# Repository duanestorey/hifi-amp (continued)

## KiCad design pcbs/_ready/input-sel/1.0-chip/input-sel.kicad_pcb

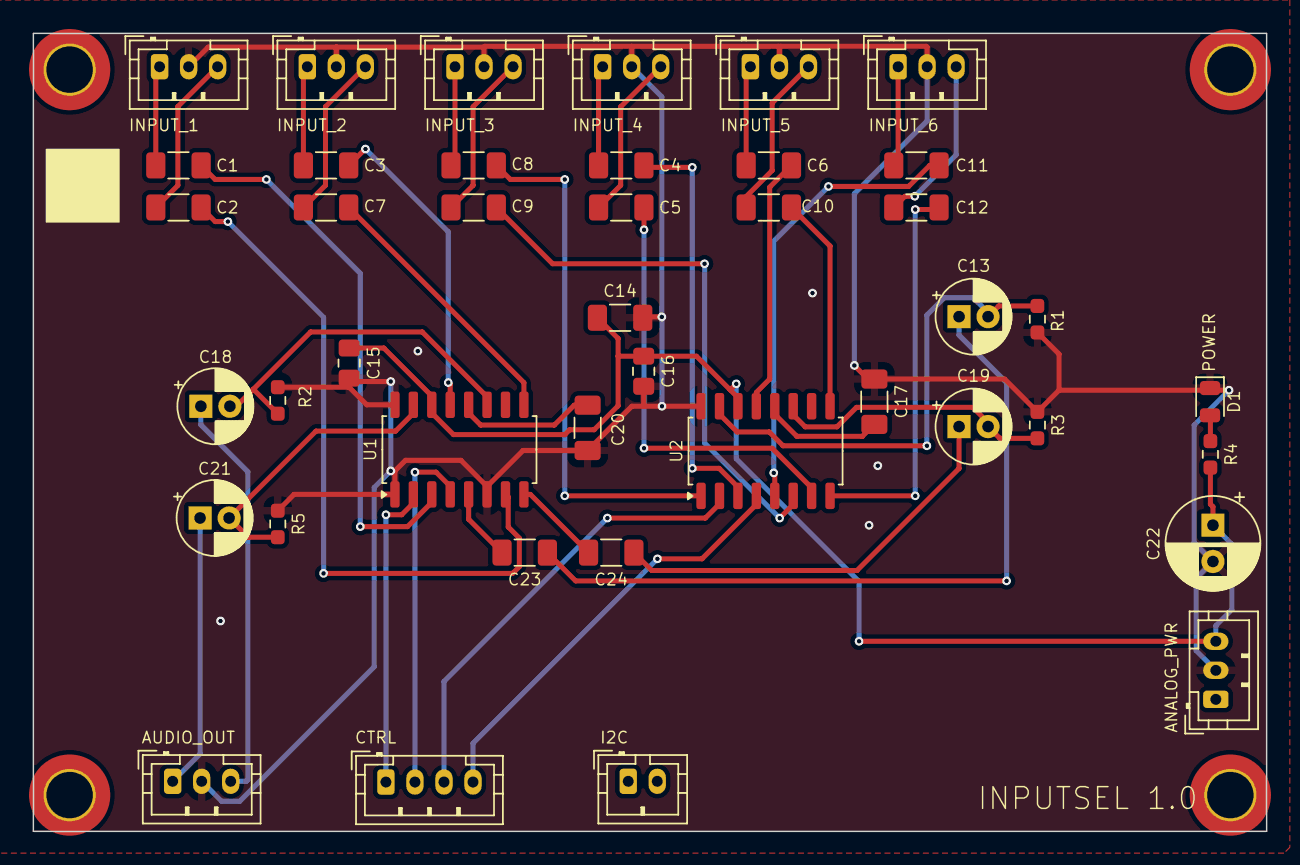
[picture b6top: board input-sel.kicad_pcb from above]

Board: 2 copper layers, 85.0 x 55.0 mm, 46 parts (0 on the bottom side), 43 nets.

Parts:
C1, C2, C3, C4, C5, C6, C7, C8, C9, C10, C11, C12, C23, C24: 0.1u 50V C0G; C_1206_3216Metric_Pad1.33x1.80mm_HandSolder
C13, C18, C19, C21: 4.7u 35V Nichicon Muse; CP_Radial_D5.0mm_P2.00mm
C14, C17, C20: 10U; C_1206_3216Metric_Pad1.33x1.80mm_HandSolder
C15, C16: 0.1u; C_0805_2012Metric_Pad1.18x1.45mm_HandSolder
C22: 470u; CP_Radial_D6.3mm_P2.50mm
D1: RED; LED_0805_2012Metric
H1, H2, H3, H4: MountingHole; MountingHole_3.2mm_M3_DIN965_Pad_TopOnly
J1, J2, J3, J4, J5, J6, J8: Conn_01x03_Pin; JST_PH_B3B-PH-K_1x03_P2.00mm_Vertical
J7: Conn_01x03_Male; JST_PH_B3B-PH-K_1x03_P2.00mm_Vertical
J9: Conn_01x04_Pin; JST_PH_B4B-PH-K_1x04_P2.00mm_Vertical
J10: Conn_01x02_Male; JST_PH_B2B-PH-K_1x02_P2.00mm_Vertical
R1, R2, R3, R5: 100K; R_0603_1608Metric_Pad0.98x0.95mm_HandSolder
R4: 75R; R_0603_1608Metric_Pad0.98x0.95mm_HandSolder
U1, U2: NJM2750; SOP-16_4.4x10.4mm_P1.27mm

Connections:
AGND: C14.2, C15.2, C16.2, C17.1, C20.1, C22.2, D1.1 (K), J1.2, J2.2, J3.2, J4.2, J5.2, J6.2, J7.2, J8.2, R1.1, R2.1, R3.1, R5.1, U1.1 (IN1L), U1.6 (IN1R), U1.16 (GND), U2.16 (GND)
CTRL1: J9.1, U1.2 (CNT1)
CTRL2: J9.2, U1.4 (CNT2)
CTRL3: J9.3, U2.2 (CNT1)
CTRL4: J9.4, U2.4 (CNT2)
EXPAND_L: C13.1, C23.1
EXPAND_R: C19.1, C24.1
unnamed: C11.2, U2.5 (IN4L)
unnamed: C12.2, U2.8 (IN4L)
unnamed: C23.2, U1.5 (IN4L)
unnamed: C24.2, U1.8 (IN4L)
unnamed: D1.2 (A), R4.1
unnamed: C1.2, U1.3 (IN2L)
unnamed: C2.2, U1.7 (IN2R)
unnamed: C3.2, U1.13 (IN3L)
unnamed: C7.2, U1.9 (IN3R)
unnamed: C21.2, R5.2, U1.15 (OUTL)
unnamed: C18.2, R2.2, U1.11 (OUTR)
unnamed: C20.2, U1.12 (VREF)
unnamed: C8.2, U2.1 (IN1L)
unnamed: C9.2, U2.6 (IN1R)
unnamed: C4.2, U2.3 (IN2L)
unnamed: C5.2, U2.7 (IN2R)
unnamed: C6.2, U2.13 (IN3L)
unnamed: C10.2, U2.9 (IN3R)
unnamed: C13.2, R1.2, U2.15 (OUTL)
unnamed: C19.2, R3.2, U2.11 (OUTR)
unnamed: C17.2, U2.12 (VREF)
OUT_L: C21.1, J8.1
OUT_R: C18.1, J8.3
RCA1_L: C1.1, J1.1
RCA1_R: C2.1, J1.3
RCA2_L: C3.1, J2.1
RCA2_R: C7.1, J2.3
RCA3_L: C8.1, J3.1
RCA3_R: C9.1, J3.3
RCA4_L: C4.1, J4.1
RCA4_R: C5.1, J4.3
RCA5_L: C6.1, J5.1
RCA5_R: C10.1, J5.3
RCA6_L: C11.1, J6.1
RCA6_R: C12.1, J6.3
V+: C14.1, C15.1, C16.1, C22.1, J7.3, R4.2, U1.14 (V+), U2.14 (V+)

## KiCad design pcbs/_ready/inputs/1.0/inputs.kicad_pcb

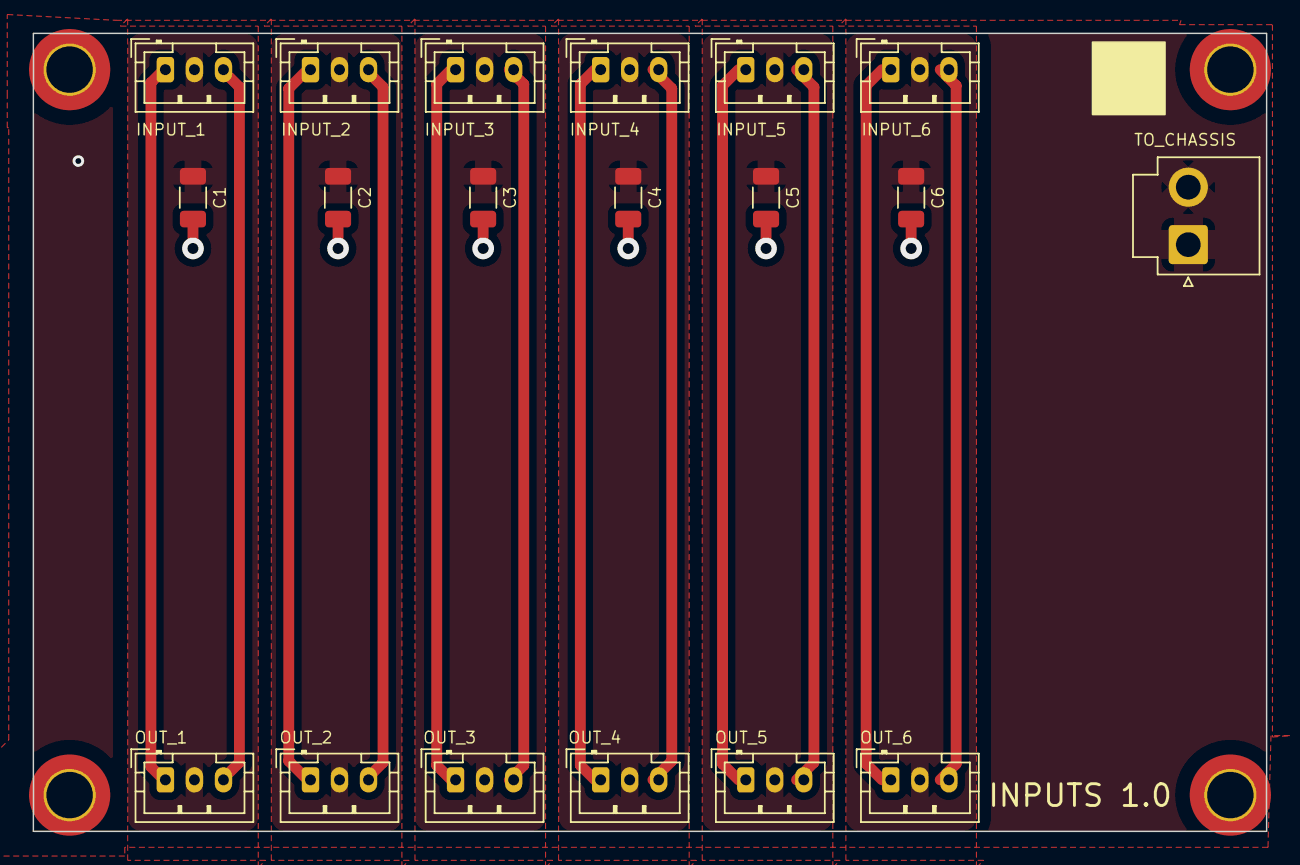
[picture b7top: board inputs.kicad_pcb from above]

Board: 2 copper layers, 85.0 x 55.0 mm, 23 parts (0 on the bottom side), 19 nets.

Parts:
C1, C2, C3, C4, C5, C6: 0.1u 100V; C_1206_3216Metric
H1, H2, H3, H4: MountingHole; MountingHole_3.2mm_M3_DIN965_Pad_TopOnly
J1, J2, J3, J4, J5, J6, J7, J8, J9, J10, J11, J12: Conn_01x03_Pin; JST_PH_B3B-PH-K_1x03_P2.00mm_Vertical
J13: Conn_01x02_Pin; JST_VH_B2P-VH-B_1x02_P3.96mm_Vertical

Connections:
GND_1: C1.1, J1.2, J7.2
GND_2: C2.1, J3.2, J8.2
GND_3: C3.1, J5.2, J9.2
GND_4: C4.1, J2.2, J10.2
GND_5: C5.1, J4.2, J11.2
GND_6: C6.1, J6.2, J12.2
LEFT_1: J1.1, J7.1
LEFT_2: J3.1, J8.1
LEFT_3: J5.1, J9.1
LEFT_4: J2.1, J10.1
LEFT_5: J4.1, J11.1
LEFT_6: J6.1, J12.1
PGND: C1.2, C2.2, C3.2, C4.2, C5.2, C6.2, J13.1, J13.2
RIGHT_1: J1.3, J7.3
RIGHT_2: J3.3, J8.3
RIGHT_3: J5.3, J9.3
RIGHT_4: J2.3, J10.3
RIGHT_5: J4.3, J11.3
RIGHT_6: J6.3, J12.3

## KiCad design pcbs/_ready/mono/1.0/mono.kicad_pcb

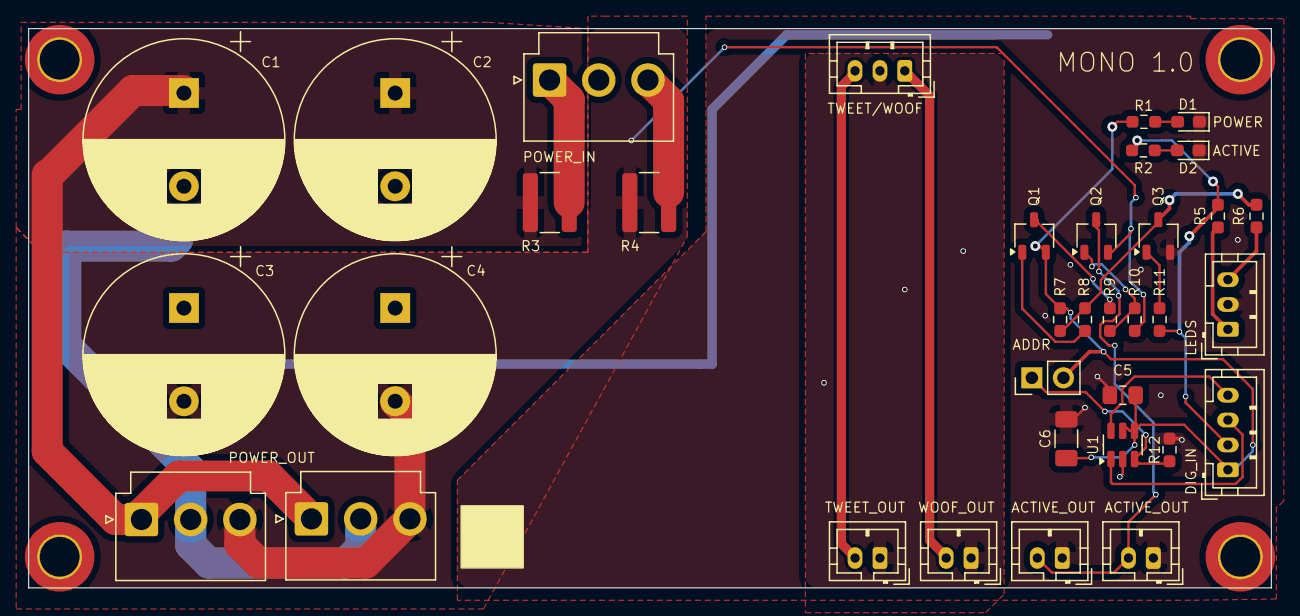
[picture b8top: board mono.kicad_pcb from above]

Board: 2 copper layers, 100.0 x 45.0 mm, 39 parts (0 on the bottom side), 23 nets.

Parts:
C1, C2, C3, C4: 2200u 50V; CP_Radial_D16.0mm_P7.50mm
C5: 0.1u; C_0805_2012Metric_Pad1.18x1.45mm_HandSolder
C6: 10u; C_1206_3216Metric_Pad1.33x1.80mm_HandSolder
D1: BLUE; LED_0603_1608Metric_Pad1.05x0.95mm_HandSolder
D2: RED; LED_0603_1608Metric_Pad1.05x0.95mm_HandSolder
H1, H2, H3, H4: MountingHole; MountingHole_3.2mm_M3_DIN965_Pad_TopOnly
J1, J3: Conn_01x03_Pin; JST_PH_B3B-PH-K_1x03_P2.00mm_Vertical
J2, J6, J7: Conn_01x03_Male; JST_VH_B3P-VH-B_1x03_P3.96mm_Vertical
J4: Conn_01x02_Pin; PinHeader_1x02_P2.54mm_Vertical
J5: Conn_01x04_Pin; JST_PH_B4B-PH-K_1x04_P2.00mm_Vertical
J8, J9, J10, J11: Conn_01x02_Pin; JST_PH_B2B-PH-K_1x02_P2.00mm_Vertical
Q1: BC807; TSOT-23
Q2, Q3: BC817K-40; TSOT-23
R1, R6: 150R; R_0603_1608Metric_Pad0.98x0.95mm_HandSolder
R2: 300R; R_0603_1608Metric_Pad0.98x0.95mm_HandSolder
R3, R4: 470m 3W; R_1218_3246Metric_Pad1.22x4.75mm_HandSolder
R5: 550R; R_0603_1608Metric_Pad0.98x0.95mm_HandSolder
R7: 10k; R_0603_1608Metric_Pad0.98x0.95mm_HandSolder
R8, R11: 1K; R_0603_1608Metric_Pad0.98x0.95mm_HandSolder
R9: 100K; R_0603_1608Metric_Pad0.98x0.95mm_HandSolder
R10: 50K; R_0603_1608Metric_Pad0.98x0.95mm_HandSolder
R12: 4.7k; R_0603_1608Metric_Pad0.98x0.95mm_HandSolder
U1: TMP100; SOT-23-6

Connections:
3V3: C5.1, C6.1, J4.2, J5.1, Q1.2 (E), R1.2, R7.2, U1.4 (V+), U1.5 (ADD0)
ACTIVE_IN: J5.2, R2.2, R5.2, R11.1
ACTIVE_NEG: Q3.3 (C), R6.2, R7.1, R8.1
ACTIVE_OUT: J10.2, J11.2, Q2.3 (C)
AGND: J1.2, J8.1, J9.1
LED_ACTIVE: J3.1, R5.1
LED_STANDBY: J3.3, R6.1
NEG: C3.2, C4.2, J6.3, J7.3, Q2.2 (E), R4.2, R10.1
unnamed: D1.2 (A), R1.1
unnamed: D2.2 (A), R2.1
unnamed: J4.1, R12.1, U1.3 (ADD1)
unnamed: Q1.1 (B), R8.2
unnamed: Q1.3 (C), R9.2
unnamed: Q2.1 (B), R9.1, R10.2
unnamed: Q3.1 (B), R11.2
PGND: C1.2, C2.2, C3.1, C4.1, C5.2, C6.2, D1.1 (K), D2.1 (K), J2.2, J3.2, J6.2, J7.2, J10.1, J11.1, Q3.2 (E), R12.2, U1.2 (GND)
POS: C1.1, C2.1, J6.1, J7.1, R3.2
SCL: J5.3, U1.1 (SCL)
SDA: J5.4, U1.6 (SDA)
TWEETER: J1.3, J8.2
VM: J2.3, R4.1
VP: J2.1, R3.1
WOOFER: J1.1, J9.2
